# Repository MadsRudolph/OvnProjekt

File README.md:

# 🔥 Ovn-Projekt — Pure Analog & Digital Oven Controller (No MCU)

A fully hardware-based oven control system designed and built with **analog + digital electronics** only — **no microcontroller** or pre-programmed ICs.  
All schematics and PCBs were created in **KiCad**. The final project uses a **hierarchical schematic** so all subsystems connect cleanly in one place.

> This was a tough one: we built the oven before learning every theory detail in class. That made it frustrating at times — and incredibly satisfying when everything finally worked.

---

## 🚀 Quick Start (Open the Project)

1. Open **KiCad 7/8** (tested with 8).
2. Open the **main project**:
   - `./OVN/OVN.kicad_pro`
3. Open the **top schematic**:
   - `./OVN/OVN.kicad_sch`  
   This is the top-level design with a **hierarchical sheet** that pulls in all subsystems (analog control, digital timing/state machine, deviation display, oscillator).
4. Optional: open the **PCB**:
   - `./OVN/OVN.kicad_pcb`

> The subfolders contain **intermediate/local variants** and backups. They’re useful for history, but the **final connected design** lives in `OVN/`.

---

## 🎯 Project Goals

- Automatically cycle between **three set temperatures** (e.g., 50 °C → 110 °C → 80 °C → repeat)
- Hold each temperature for a **fixed duration** (e.g., ~80 s)
- Maintain temperature within **±1 °C** of the target
- Provide **safety shutdown** above a critical threshold (e.g., 130 °C)
- Show **real-time temperature deviation** on an LED bar
- Implement everything with **discrete analog + digital logic** (no MCU/firmware)

---

## 🧩 System Overview

The oven control system is composed of **four main subsystems**:

### 1) Digital Oscillator
Generates clock signals for counters/timers and ADC timing.
- RC network + digital logic
- Adjustable frequency outputs
- Example board size around *35 mm × 47 mm*

### 2) Deviation Display (Afvigelsesdisplay)
Real-time visualization of error between current temperature and setpoint.
- **ADC0804** A/D converter
- **Two 74HC238** decoders → **16 LEDs**
- Center LEDs ≈ in-range (green), outer LEDs ≈ negative/positive deviation

### 3) Analog Control Circuit
Compares measured temperature to selected setpoint and drives the heater.
- Sensor: **LM35**
- **Op-amps** for differential amplification & comparators for thresholds
- **CD4066** analog switch selects between three setpoints
- Provides a scaled signal for the deviation display

### 4) Digital State Machine & Timing
Sequences the temperature program and dwell times.
- **74HC163** counters + combinational logic
- Generates `T1/T2/T3` signals for setpoint selection
- Drives indicators (LEDs / 7-segment) and coordinates timing

---
<h2>🧾 Project Poster</h2>
<p align="center">
  
  <br>
  <em>Click to open the full PDF</em>
</p>
---
## 🛠 Tools & Key Components

- **Design:** KiCad (schematic + PCB)
- **Test Gear:** Multimeter, oscilloscope, logic probes/analyzers
- **Key ICs/Parts:** LM35, ADC0804, 74HC238, 74HC163, CD4066, MCP6002, passives, LEDs

---

## ⚡ Workflow

1. **Subsystem Breadboarding** → validate analog thresholds, timing, and LED decoding  
2. **KiCad Schematic & PCB** → create/clean symbols and **custom footprints** as needed  
3. **Integration** → hierarchical sheet in `OVN` ties everything together  
4. **Debug & Iterate** → scope timing edges, adjust thresholds, verify stability and safety

---

## 🌟 Key Learnings

- Designing robust control with **only analog/digital logic** (no firmware safety net)
- Practical timing, noise, and threshold trade-offs in real hardware
- **KiCad** hierarchical design, footprint creation, and multi-board bring-up
- System-level debugging with mixed-signal interactions

---

## 👥 Team

- **Mads Vølkers Rudolph**  
- **Jonas Beck Jensen**
- **Sigurd Hestbech**
- **Andreas Skaaning**

---

## 🚀 Future Improvements

- MCU-based mode for flexible profiles + logging (keeping the analog chain as backup)
- PID/PI control for even tighter regulation
- Small display (OLED/LCD) with progress and temperature graphs

---

## 🏁 Result

The integrated **OVN** project reflects the **final working oven**:  
- Automatic multi-temperature cycling with dwell times  
- Safety cutoff behavior verified  
- Deviation display and timing logic functioning reliably

**No MCU. Just electrons doing the choreography.**

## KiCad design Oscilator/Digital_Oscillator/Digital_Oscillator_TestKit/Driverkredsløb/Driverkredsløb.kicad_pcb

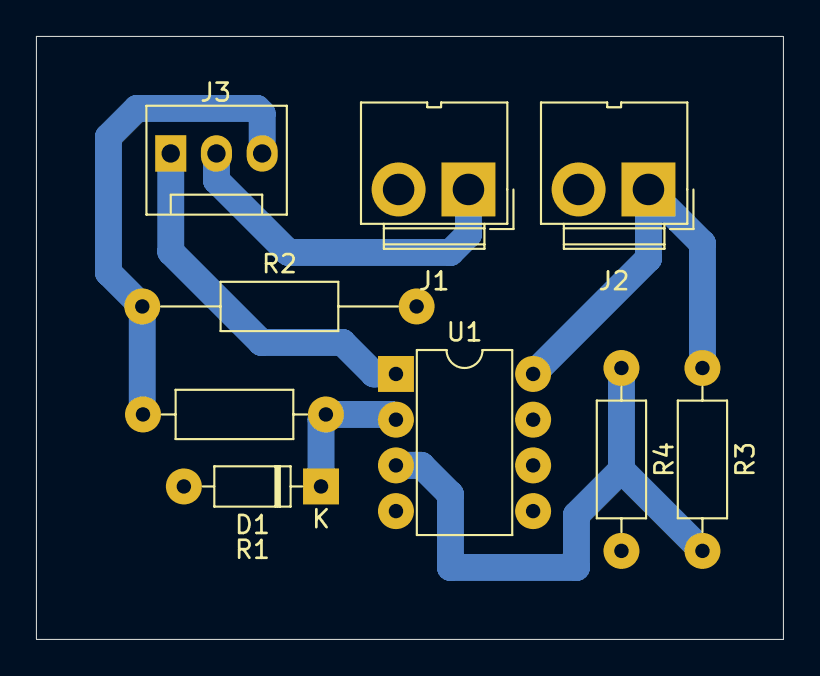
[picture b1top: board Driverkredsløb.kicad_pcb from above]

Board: 2 copper layers, 41.5 x 33.5 mm, 9 parts (0 on the bottom side), 7 nets.

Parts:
D1: 1N4148; D_DO-35_SOD27_P7.62mm_Horizontal
J1, J2: Conn_01x02_Socket; JWT_A3963_1x02_P3.96mm_Vertical
J3: Conn_01x03_Socket; FanPinHeader_1x03_P2.54mm_Vertical
R1: 20k; R_Axial_DIN0207_L6.3mm_D2.5mm_P10.16mm_Horizontal
R2: 0.1; R_Axial_DIN0207_L6.3mm_D2.5mm_P15.24mm_Horizontal
R3: 15k; R_Axial_DIN0207_L6.3mm_D2.5mm_P10.16mm_Horizontal
R4: 300; R_Axial_DIN0207_L6.3mm_D2.5mm_P10.16mm_Horizontal
U1: MCP6002-xMC; DIP-8_W7.62mm

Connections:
GND: J1.2, J2.2, R2.2, R4.2, U1.4 (V-)
unnamed: D1.1 (K), R1.1, U1.2 (-)
unnamed: J1.1, J3.2
unnamed: J2.1, R3.1, U1.8 (V+)
unnamed: J3.1, U1.1
unnamed: J3.3, R1.2, R2.1
unnamed: R3.2, R4.1, U1.3 (+)

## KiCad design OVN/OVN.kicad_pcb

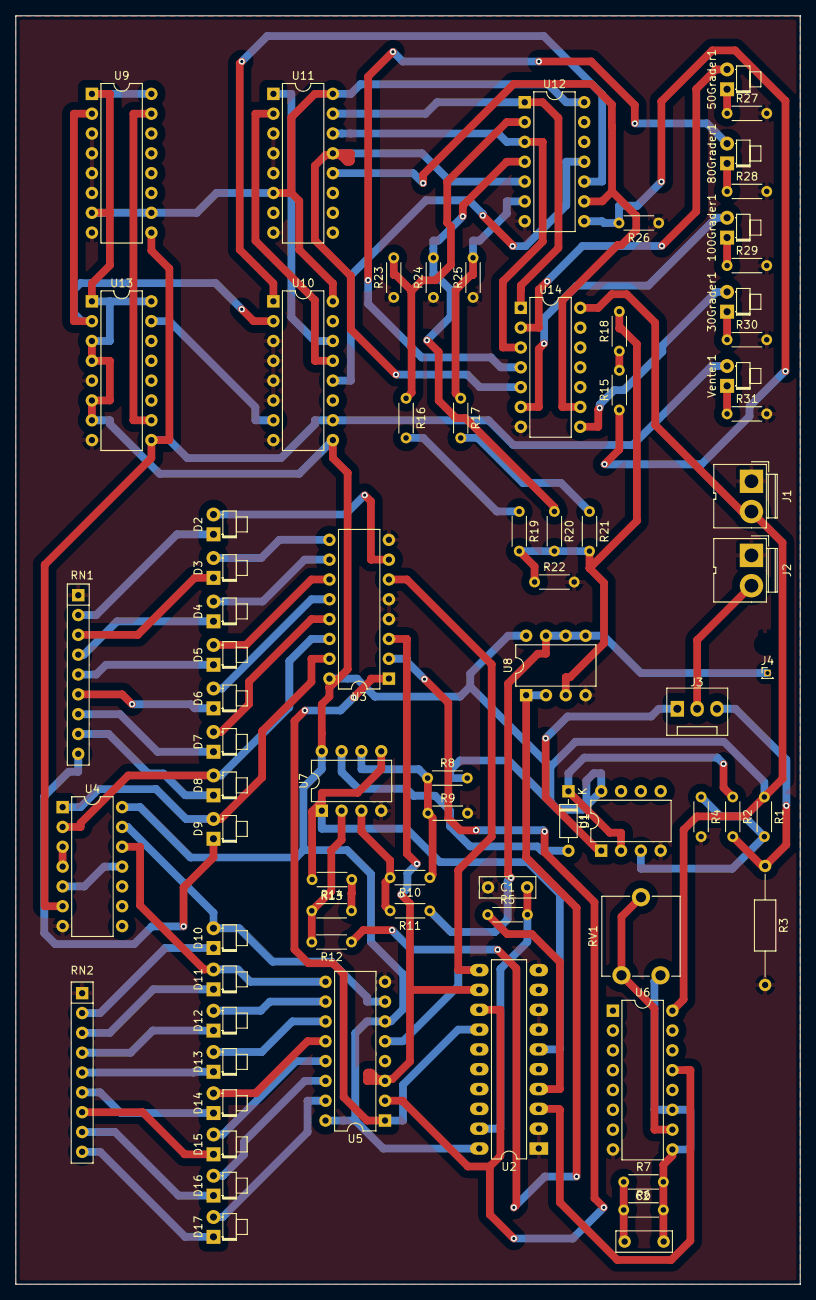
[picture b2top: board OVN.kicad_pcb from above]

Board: 2 copper layers, 100.5 x 162.5 mm, 76 parts (0 on the bottom side), 87 nets.

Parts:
30Grader1, 50Grader1, 80Grader1, 100Grader1: LED; LED_D1.8mm_W1.8mm_H2.4mm_Horizontal_O1.27mm_Z8.2mm
C1: 150nF; C_Disc_D7.0mm_W2.5mm_P5.00mm
C2: 100 nF; C_Disc_D7.0mm_W2.5mm_P5.00mm
D1: 1N4148; D_DO-35_SOD27_P7.62mm_Horizontal
D2, D4, D5, D6, D7, D12, D13, D14, D15, D16, D17: R; LED_D1.8mm_W1.8mm_H2.4mm_Horizontal_O1.27mm_Z8.2mm
D3: LED; LED_D1.8mm_W1.8mm_H2.4mm_Horizontal_O1.27mm_Z8.2mm
D8, D11: GU; LED_D1.8mm_W1.8mm_H2.4mm_Horizontal_O1.27mm_Z8.2mm
D9, D10: GR; LED_D1.8mm_W1.8mm_H2.4mm_Horizontal_O1.27mm_Z8.2mm
J1, J2: Conn_01x02_Pin; JWT_A3963_1x02_P3.96mm_Vertical
J3: Conn_01x03_Socket; FanPinHeader_1x03_P2.54mm_Vertical
J4: LM35; PinHeader_1x01_P1.00mm_Vertical
R1: 15k; R_Axial_DIN0204_L3.6mm_D1.6mm_P5.08mm_Horizontal
R2: 20k; R_Axial_DIN0204_L3.6mm_D1.6mm_P5.08mm_Horizontal
R3: 0.1; R_Axial_DIN0207_L6.3mm_D2.5mm_P15.24mm_Horizontal
R4: 300; R_Axial_DIN0204_L3.6mm_D1.6mm_P5.08mm_Horizontal
R5, R22: 100K; R_Axial_DIN0204_L3.6mm_D1.6mm_P5.08mm_Horizontal
R6: 4.3k; R_Axial_DIN0204_L3.6mm_D1.6mm_P5.08mm_Horizontal
R7: 123K6; R_Axial_DIN0204_L3.6mm_D1.6mm_P5.08mm_Horizontal
R8, R9, R14: 11.5K; R_Axial_DIN0204_L3.6mm_D1.6mm_P5.08mm_Horizontal
R10, R13: 301K; R_Axial_DIN0204_L3.6mm_D1.6mm_P5.08mm_Horizontal
R11, R12: 10K; R_Axial_DIN0204_L3.6mm_D1.6mm_P5.08mm_Horizontal
R15: 787K; R_Axial_DIN0204_L3.6mm_D1.6mm_P5.08mm_Horizontal
R16: 5.6K; R_Axial_DIN0204_L3.6mm_D1.6mm_P5.08mm_Horizontal
R17: 237K; R_Axial_DIN0204_L3.6mm_D1.6mm_P5.08mm_Horizontal
R18: 15K; R_Axial_DIN0204_L3.6mm_D1.6mm_P5.08mm_Horizontal
R19: 475K; R_Axial_DIN0204_L3.6mm_D1.6mm_P5.08mm_Horizontal
R20: 300K; R_Axial_DIN0204_L3.6mm_D1.6mm_P5.08mm_Horizontal
R21: 2.6K; R_Axial_DIN0204_L3.6mm_D1.6mm_P5.08mm_Horizontal
R23, R24, R25, R26, R27, R28, R29, R30, R31: R; R_Axial_DIN0204_L3.6mm_D1.6mm_P5.08mm_Horizontal
RN1, RN2: R_Network08; R_Array_SIP9
RV1: R_Potentiometer_Small; Potentiometer_ACP_CA9-V10_Vertical
U1, U7, U8: MCP6002-xMC; DIP-8_W7.62mm
U2: ADC0804LCN; DIP-20_W7.62mm_LongPads
U3, U5: 74HC238N; DIP-16_W7.62mm
U4: SN74HC86; DIP-14_W7.62mm
U6: 74HC4060; DIP-16_W7.62mm
U9, U10, U13: SN74HC163N; DIP-16_W7.62mm
U11: 74HC138N; DIP-16_W7.62mm
U12, U14: SN74HC04N; DIP-14_W7.62mm
Venter1: LED; LED_D1.8mm_W1.8mm_H2.4mm_Horizontal_O1.27mm_Z8.2mm

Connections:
10V-30V: J2.2, J3.2
+5V: J1.2, R1.1, R8.2, U1.8 (V+), U2.20 (VCC), U3.16 (VCC), U4.14 (VCC), U5.6 (E3), U5.16 (VCC), U6.16 (VDD), U7.8 (V+), U8.8 (V+), U9.1 (~MR), U9.7 (CEP), U9.10 (CET), U9.16 (VCC), U10.9 (~LOAD), U10.16 (VCC), U11.6 (E3), U11.16 (VCC), U12.14 (VCC), U13.1 (~MR), U13.3 (D0), U13.4 (D1), U13.6 (D3), U13.7 (CEP), U13.16 (VCC), U14.14 (VCC)
/ADC Convertor/DB4: U2.14 (DB4), U3.1 (A0), U5.1 (A0)
/ADC Convertor/DB5: U2.13 (DB5), U3.2 (A1), U5.2 (A1)
/ADC Convertor/DB6: U2.12 (DB6), U3.3 (A2), U5.3 (A2)
/ADC Convertor/DB7: U2.11 (DB7), U3.6 (E3), U5.5 (~E2)
/ADC Convertor/WR_in: U2.3 (~WR), U6.13 (Q9), U9.2 (CLK), U10.2 (CLK), U13.2 (CLK)
/Afvigelsesdisplay/Steady state: U4.6 (3Y), U9.9 (~LOAD), U10.10 (CET), U13.9 (~LOAD), Venter1.2 (A)
/Analog styring Differensforstærker/V-Ovn: D1.2 (A), U7.7
/Analog styring spændingsdeler/30°C: R15.1, R26.2, U12.8 (4Y)
/Analog styring spændingsdeler/50°C: R16.1, R23.2, U12.2 (1Y)
/Analog styring spændingsdeler/80°C: R20.1, R24.2, U12.4 (2Y)
/Analog styring spændingsdeler/100°C: R17.1, R25.2, U12.6 (3Y)
Afv_displ_adc: R14.2, U2.6 (VIN(+)), U7.1, U7.5 (+)
GND: C1.1, J1.1, J2.1, R3.2, R4.2, R9.2, R22.2, R23.1, R24.1, R25.1, R26.1, R27.2, R28.2, R29.2, R30.2, R31.2, RN1.1 (common), RN2.1 (common), U1.4 (V-), U2.1 (~CS), U2.2 (~RD), U2.7 (VIN(-)), U2.8 (AGND), U2.10 (DGND), U3.4 (~E1), U3.5 (~E2), U3.8 (GND), U4.7 (GND), U5.4 (~E1), U5.8 (GND), U6.8 (VSS), U6.12 (CLR), U7.4 (V-), U8.4 (V-), U9.3 (D0), U9.4 (D1), U9.5 (D2), U9.6 (D3), U9.8 (GND), U10.3 (D0), U10.4 (D1), U10.5 (D2), U10.6 (D3), U10.8 (GND), U11.3 (A2), U11.4 (~E1), U11.5 (~E2), U11.8 (GND), U12.7 (GND), U13.5 (D2), U13.8 (GND), U14.7 (GND)
LM35_out: J4.1, R11.1, U8.5 (+), U8.6 (-), U8.7
unnamed: 30Grader1.2 (A), U14.8 (4Y)
unnamed: 30Grader1.1 (K), R30.1
unnamed: 50Grader1.2 (A), U14.2 (1Y)
unnamed: 50Grader1.1 (K), R27.1
unnamed: 80Grader1.2 (A), U14.4 (2Y)
unnamed: 80Grader1.1 (K), R28.1
unnamed: 100Grader1.2 (A), U14.6 (3Y)
unnamed: 100Grader1.1 (K), R29.1
unnamed: C2.1, R6.1, R7.1
unnamed: D1.1 (K), R2.1, U1.2 (-)
unnamed: D2.2 (A), U3.7 (Y7)
unnamed: D2.1 (K), RN1.2 (R1)
unnamed: D3.2 (A), U3.9 (Y6)
unnamed: D3.1 (K), RN1.3 (R2)
unnamed: D4.2 (A), U3.10 (Y5)
unnamed: D4.1 (K), RN1.4 (R3)
unnamed: D5.2 (A), U3.11 (Y4)
unnamed: D5.1 (K), RN1.5 (R4)
unnamed: D6.2 (A), U3.12 (Y3)
unnamed: D6.1 (K), RN1.6 (R5)
unnamed: D7.2 (A), U3.13 (Y2)
unnamed: D7.1 (K), RN1.7 (R6)
unnamed: D8.2 (A), U3.14 (Y1), U4.2 (1Y)
unnamed: D8.1 (K), RN1.8 (R7)
unnamed: D9.2 (A), U3.15 (Y0), U4.1 (1A)
unnamed: D9.1 (K), RN1.9 (R8)
unnamed: D10.2 (A), U4.13 (6A), U5.7 (Y7)
unnamed: D10.1 (K), RN2.2 (R1)
unnamed: D11.2 (A), U4.12 (6Y), U5.9 (Y6)
unnamed: D11.1 (K), RN2.3 (R2)
unnamed: D12.2 (A), U5.10 (Y5)
unnamed: D12.1 (K), RN2.4 (R3)
unnamed: D13.2 (A), U5.11 (Y4)
unnamed: D13.1 (K), RN2.5 (R4)
unnamed: D14.2 (A), U5.12 (Y3)
unnamed: D14.1 (K), RN2.6 (R5)
unnamed: D15.2 (A), U5.13 (Y2)
unnamed: D15.1 (K), RN2.7 (R6)
unnamed: D16.2 (A), U5.14 (Y1)
unnamed: D16.1 (K), RN2.8 (R7)
unnamed: D17.2 (A), U5.15 (Y0)
unnamed: D17.1 (K), RN2.9 (R8)
unnamed: J3.1, U1.1
unnamed: J3.3, R2.2, R3.1
unnamed: R13.2, R14.1
unnamed: R15.2, R18.1
unnamed: R16.2, R19.1
unnamed: R17.2, R21.1
unnamed: R1.2, R4.1, U1.3 (+)
unnamed: R5.1, U2.4 (CLK_IN)
unnamed: C1.2, R5.2, U2.19 (CLK_R)
unnamed: U4.3 (2A), U4.4 (2Y)
unnamed: U4.5 (3A), U4.11 (5A)
unnamed: C2.2, R6.2, R7.2, RV1.1, U6.9 (~Φ0), U6.11 (~Φ1)
unnamed: RV1.2, RV1.3, U6.10 (Φ0)
unnamed: R10.2, R11.2, U7.3 (+)
unnamed: R12.2, R13.1, U7.2 (-)
unnamed: R8.1, R9.1, R10.1, U7.6 (-)
unnamed: R18.2, R19.2, R20.2, R21.2, R22.1, U8.3 (+)
unnamed: U10.7 (CEP), U13.15 (TC)
unnamed: U10.14 (Q0), U11.1 (A0)
unnamed: U10.13 (Q1), U11.2 (A1)
unnamed: U10.12 (Q2), U12.11 (5A)
unnamed: U10.1 (~MR), U12.10 (5Y)
unnamed: U11.15 (Y0), U12.1 (1A), U14.1 (1A)
unnamed: U11.14 (Y1), U12.3 (2A), U14.3 (2A)
unnamed: U11.13 (Y2), U12.5 (3A), U14.5 (3A)
unnamed: U11.12 (Y3), U12.9 (4A), U14.9 (4A)
unnamed: U9.15 (TC), U13.10 (CET)
unnamed: R31.1, Venter1.1 (K)
Sp_v: R12.1, U8.1, U8.2 (-)

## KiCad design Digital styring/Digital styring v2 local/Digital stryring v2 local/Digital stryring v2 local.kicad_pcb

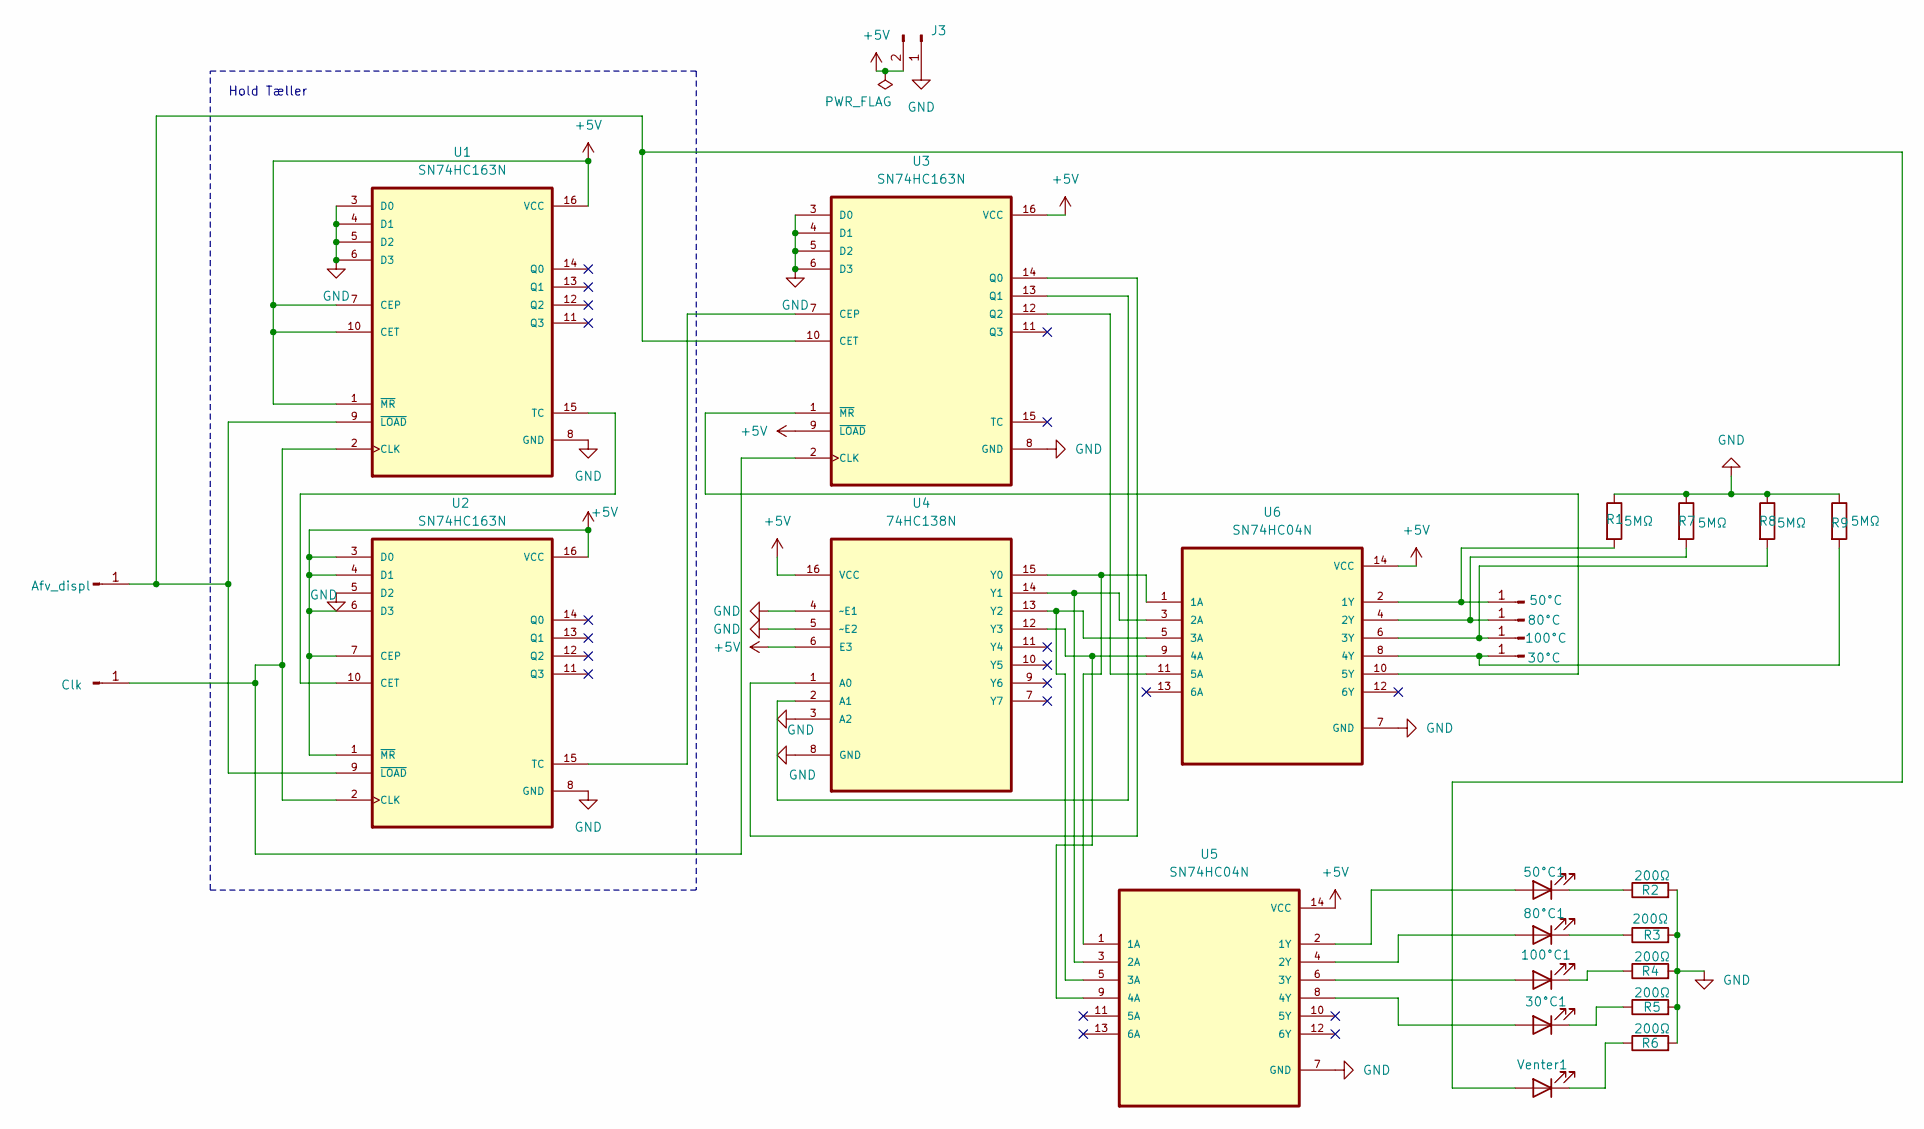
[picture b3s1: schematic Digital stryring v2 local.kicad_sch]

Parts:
30°C1, 50°C1, 80°C1, 100°C1: LED; LED_D1.8mm_W1.8mm_H2.4mm_Horizontal_O1.27mm_Z8.2mm
J1: Afv_displ; PinHeader_1x01_P1.00mm_Vertical
J2: Clk; PinHeader_1x01_P1.00mm_Vertical
J3: Conn_01x02_Pin; JWT_A3963_1x02_P3.96mm_Vertical
J4: 50°C; PinHeader_1x01_P1.00mm_Vertical
J5: 80°C; PinHeader_1x01_P1.00mm_Vertical
J6: 100°C; PinHeader_1x01_P1.00mm_Vertical
J7: 30°C; PinHeader_1x01_P1.00mm_Vertical
R1, R7, R8, R9: 5MΩ; R_Axial_DIN0204_L3.6mm_D1.6mm_P7.62mm_Horizontal
R2, R3, R4, R5, R6: 200Ω; R_Axial_DIN0204_L3.6mm_D1.6mm_P5.08mm_Horizontal
U1, U2, U3: SN74HC163N; DIP-16_W7.62mm
U4: 74HC138N; DIP-16_W7.62mm; MPN 74HC238N
U5, U6: SN74HC04N; DIP-14_W7.62mm
Venter1: LED; LED_D1.8mm_W1.8mm_H2.4mm_Horizontal_O1.27mm_Z8.2mm

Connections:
+5V: J3.2, U1.1 (~MR), U1.7 (CEP), U1.10 (CET), U1.16 (VCC), U2.1 (~MR), U2.3 (D0), U2.4 (D1), U2.6 (D3), U2.7 (CEP), U2.16 (VCC), U3.9 (~LOAD), U3.16 (VCC), U4.6 (E3), U4.16 (VCC), U5.14 (VCC), U6.14 (VCC)
GND: J3.1, R1.1, R2.2, R3.2, R4.2, R5.2, R6.2, R7.1, R8.1, R9.1, U1.3 (D0), U1.4 (D1), U1.5 (D2), U1.6 (D3), U1.8 (GND), U2.5 (D2), U2.8 (GND), U3.3 (D0), U3.4 (D1), U3.5 (D2), U3.6 (D3), U3.8 (GND), U4.3 (A2), U4.4 (~E1), U4.5 (~E2), U4.8 (GND), U5.7 (GND), U6.7 (GND)
unnamed: 30°C1.2 (A), U5.8 (4Y)
unnamed: 30°C1.1 (K), R5.1
unnamed: 50°C1.2 (A), U5.2 (1Y)
unnamed: 50°C1.1 (K), R2.1
unnamed: 80°C1.2 (A), U5.4 (2Y)
unnamed: 80°C1.1 (K), R3.1
unnamed: 100°C1.2 (A), U5.6 (3Y)
unnamed: 100°C1.1 (K), R4.1
unnamed: J1.1, U1.9 (~LOAD), U2.9 (~LOAD), U3.10 (CET), Venter1.2 (A)
unnamed: J2.1, U1.2 (CLK), U2.2 (CLK), U3.2 (CLK)
unnamed: J4.1, R1.2, U6.2 (1Y)
unnamed: J5.1, R7.2, U6.4 (2Y)
unnamed: J6.1, R8.2, U6.6 (3Y)
unnamed: J7.1, R9.2, U6.8 (4Y)
unnamed: U1.15 (TC), U2.10 (CET)
unnamed: U2.15 (TC), U3.7 (CEP)
unnamed: U3.14 (Q0), U4.1 (A0)
unnamed: U3.13 (Q1), U4.2 (A1)
unnamed: U3.12 (Q2), U6.11 (5A)
unnamed: U3.1 (~MR), U6.10 (5Y)
unnamed: U4.15 (Y0), U5.1 (1A), U6.1 (1A)
unnamed: U4.14 (Y1), U5.3 (2A), U6.3 (2A)
unnamed: U4.13 (Y2), U5.5 (3A), U6.5 (3A)
unnamed: U4.12 (Y3), U5.9 (4A), U6.9 (4A)
unnamed: R6.1, Venter1.1 (K)

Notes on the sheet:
Hold Tæller

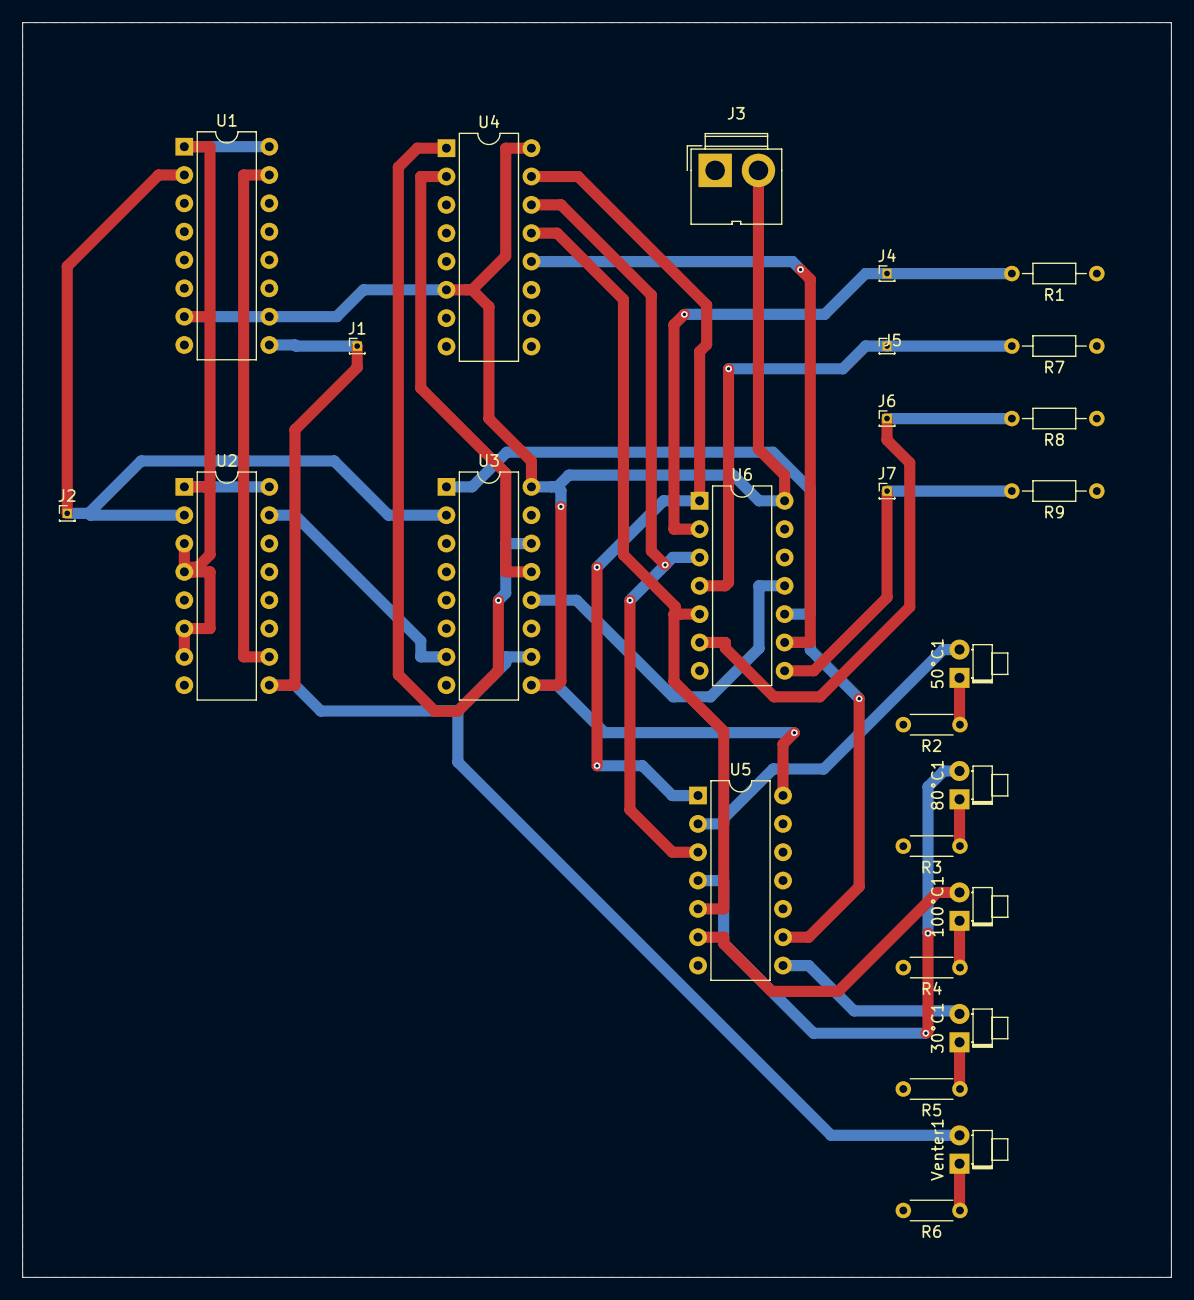
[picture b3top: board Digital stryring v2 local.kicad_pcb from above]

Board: 2 copper layers, 103.0 x 112.5 mm, 27 parts (0 on the bottom side), 27 nets.

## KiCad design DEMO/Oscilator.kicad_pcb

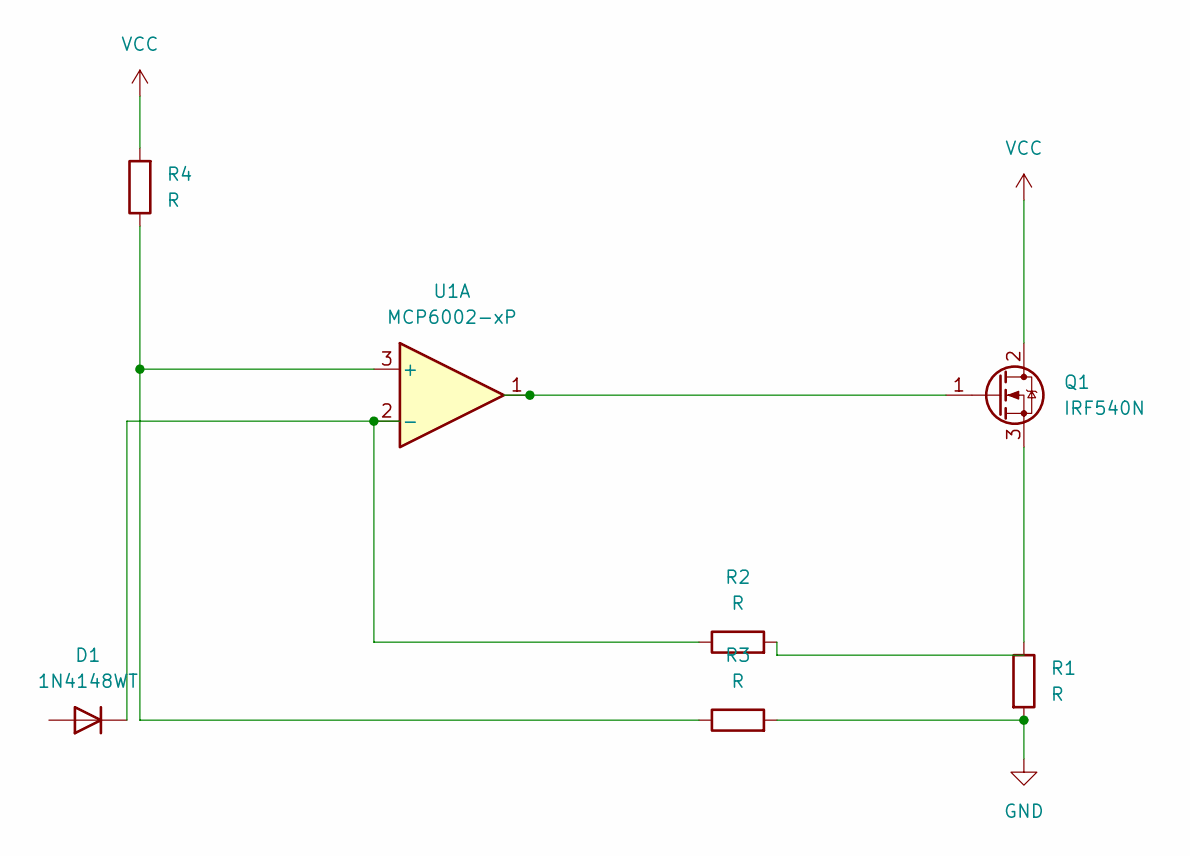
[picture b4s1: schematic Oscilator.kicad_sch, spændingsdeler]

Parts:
D1: 1N4148WT; D_SOD-523
Q1: IRF540N; TO-220-3_Vertical
R1, R2, R3, R4: R; R_Axial_DIN0207_L6.3mm_D2.5mm_P7.62mm_Horizontal
U1: MCP6002-xP; CERDIP-8_W7.62mm_SideBrazed_Socket

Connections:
GND: R1.2, R3.2
unnamed: D1.1 (K), R2.1, U1.2 (-)
unnamed: Q1.1 (G), U1.1
unnamed: Q1.3 (S), R1.1
unnamed: R3.1, R4.1, U1.3 (+)
VCC: Q1.2 (D), R4.2

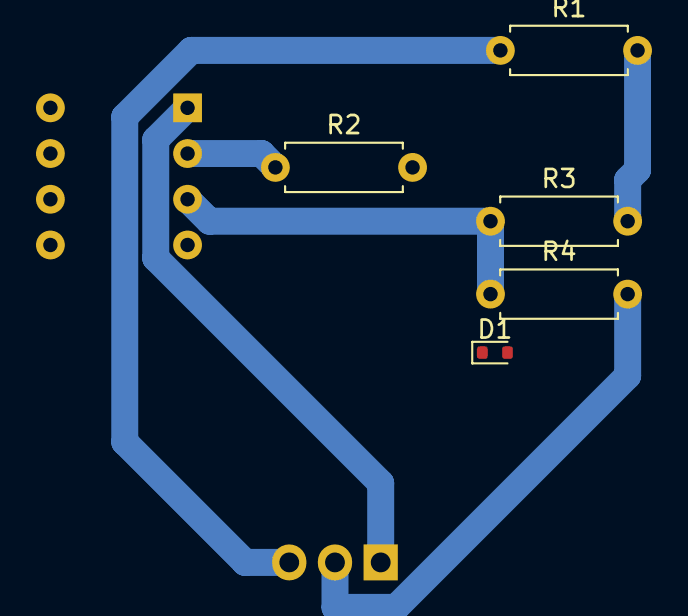
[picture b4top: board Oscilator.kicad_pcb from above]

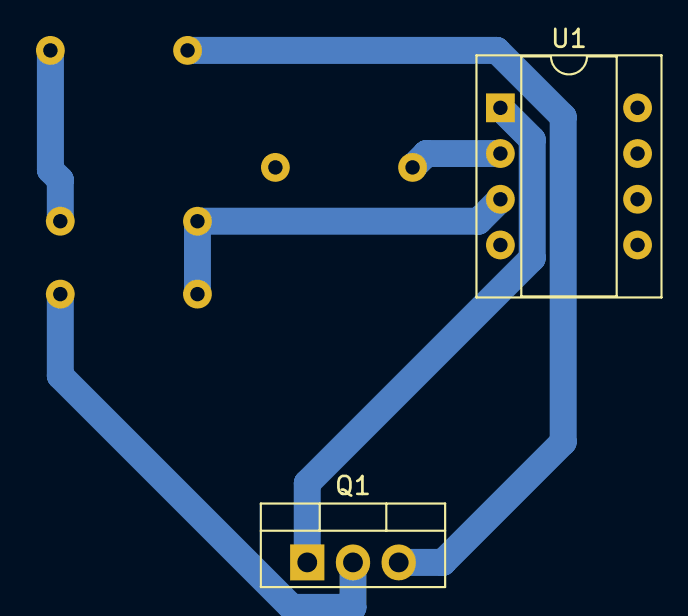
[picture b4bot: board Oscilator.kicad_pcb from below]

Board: 2 copper layers, 7 parts (2 on the bottom side), 6 nets.

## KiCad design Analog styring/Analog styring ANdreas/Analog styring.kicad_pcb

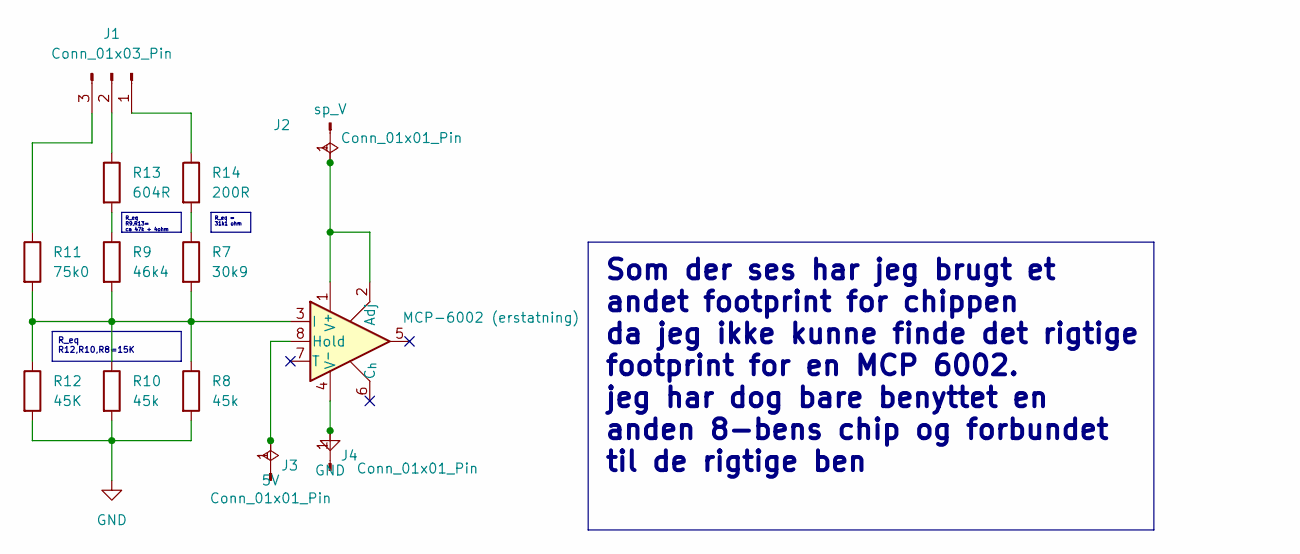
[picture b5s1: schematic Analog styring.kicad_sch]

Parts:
J1: Conn_01x03_Pin; FanPinHeader_1x03_P2.54mm_Vertical
J2, J3, J4: Conn_01x01_Pin; PinHeader_1x01_P1.00mm_Vertical
R7: 30k9; R_Axial_DIN0204_L3.6mm_D1.6mm_P2.54mm_Vertical
R8, R10: 45k; R_Axial_DIN0204_L3.6mm_D1.6mm_P2.54mm_Vertical
R9: 46k4; R_Axial_DIN0204_L3.6mm_D1.6mm_P2.54mm_Vertical
R11: 75k0; R_Axial_DIN0204_L3.6mm_D1.6mm_P2.54mm_Vertical
R12: 45K; R_Axial_DIN0204_L3.6mm_D1.6mm_P2.54mm_Vertical
R13: 604R; R_Axial_DIN0204_L3.6mm_D1.6mm_P2.54mm_Vertical
R14: 200R; R_Axial_DIN0204_L3.6mm_D1.6mm_P2.54mm_Vertical
U1: MCP-6002 (erstatning); DIP-8_W7.62mm

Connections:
GND: J4.1, R8.2, R10.2, R12.2, U1.4 (V^{-})
unnamed: J1.1, R14.1
unnamed: J1.2, R13.1
unnamed: J1.3, R11.1
unnamed: J2.1, U1.1 (V^{+}), U1.2 (Adj)
unnamed: J3.1, U1.8 (Hold)
unnamed: R9.1, R13.2
unnamed: R7.1, R14.2
unnamed: R7.2, R8.1, R9.2, R10.1, R11.2, R12.1, U1.3 (I)

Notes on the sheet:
Som der ses har jeg brugt et andet footprint for chippen da jeg ikke kunne finde det rigtige footprint for en MCP 6002. jeg har dog bare benyttet en anden 8-bens chip og forbundet til de rigtige ben
R_eq R9,R13= ca 47k + 4ohm
R_eq R12,R10,R8=15K
R_eq = 31k1 ohm

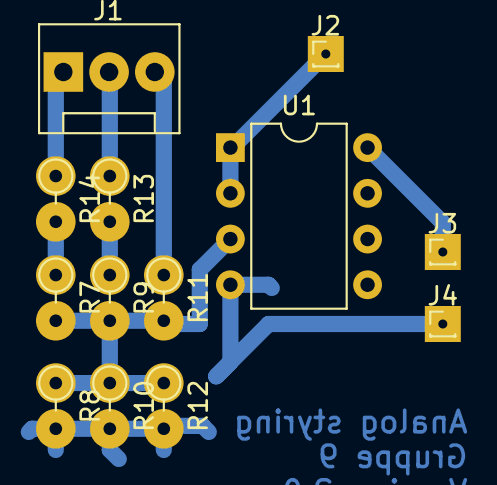
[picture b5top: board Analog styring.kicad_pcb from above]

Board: 2 copper layers, 13 parts (0 on the bottom side), 9 nets.

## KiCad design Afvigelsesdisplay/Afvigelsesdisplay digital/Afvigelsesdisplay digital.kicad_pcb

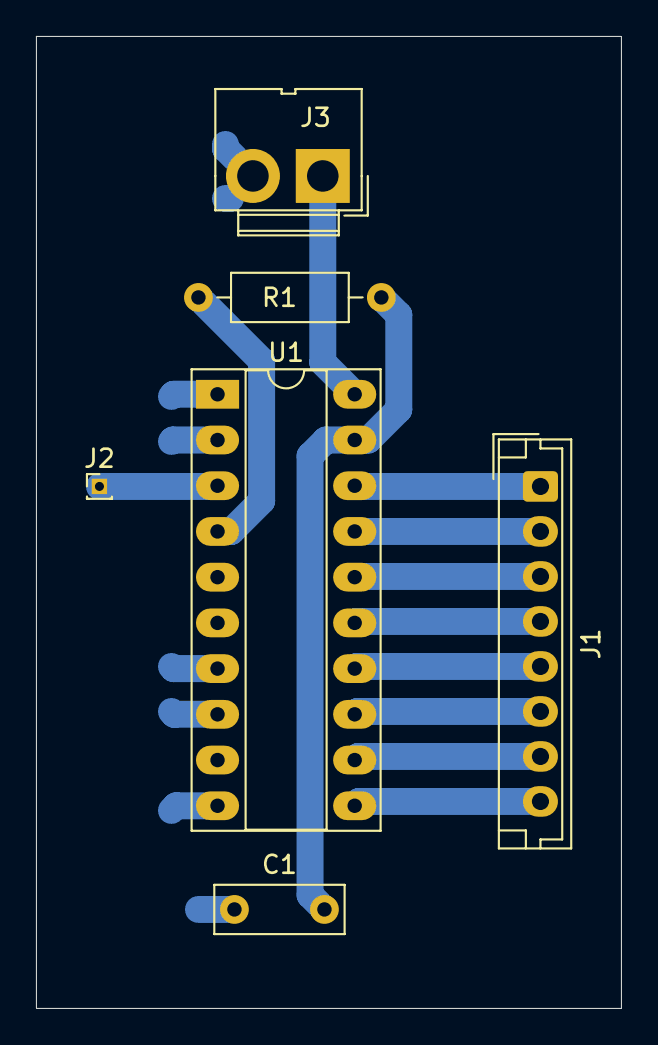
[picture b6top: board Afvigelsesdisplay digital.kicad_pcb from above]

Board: 2 copper layers, 32.5 x 54.0 mm, 6 parts (0 on the bottom side), 13 nets.

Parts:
C1: 150nF; C_Disc_D7.0mm_W2.5mm_P5.00mm
J1: Conn_01x08_Socket; JST_EH_B8B-EH-A_1x08_P2.50mm_Vertical
J2: Conn_01x01_Pin; PinHeader_1x01_P1.00mm_Vertical
J3: Conn_01x02_Pin; JWT_A3963_1x02_P3.96mm_Vertical
R1: 100K; R_Axial_DIN0207_L6.3mm_D2.5mm_P10.16mm_Horizontal
U1: ADC0804LCN; CERDIP-20_W7.62mm_SideBrazed_LongPads_Socket

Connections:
GND: C1.1, J3.2, U1.1 (~CS), U1.2 (~RD), U1.7 (VIN(-)), U1.8 (AGND), U1.10 (DGND)
unnamed: J1.1, U1.18 (DB0)
unnamed: J1.2, U1.17 (DB1)
unnamed: J1.3, U1.16 (DB2)
unnamed: J1.4, U1.15 (DB3)
unnamed: J1.5, U1.14 (DB4)
unnamed: J1.6, U1.13 (DB5)
unnamed: J1.7, U1.12 (DB6)
unnamed: J1.8, U1.11 (DB7)
unnamed: J2.1, U1.3 (~WR)
unnamed: R1.1, U1.4 (CLK_IN)
unnamed: C1.2, R1.2, U1.19 (CLK_R)
VCC: J3.1, U1.20 (VCC)

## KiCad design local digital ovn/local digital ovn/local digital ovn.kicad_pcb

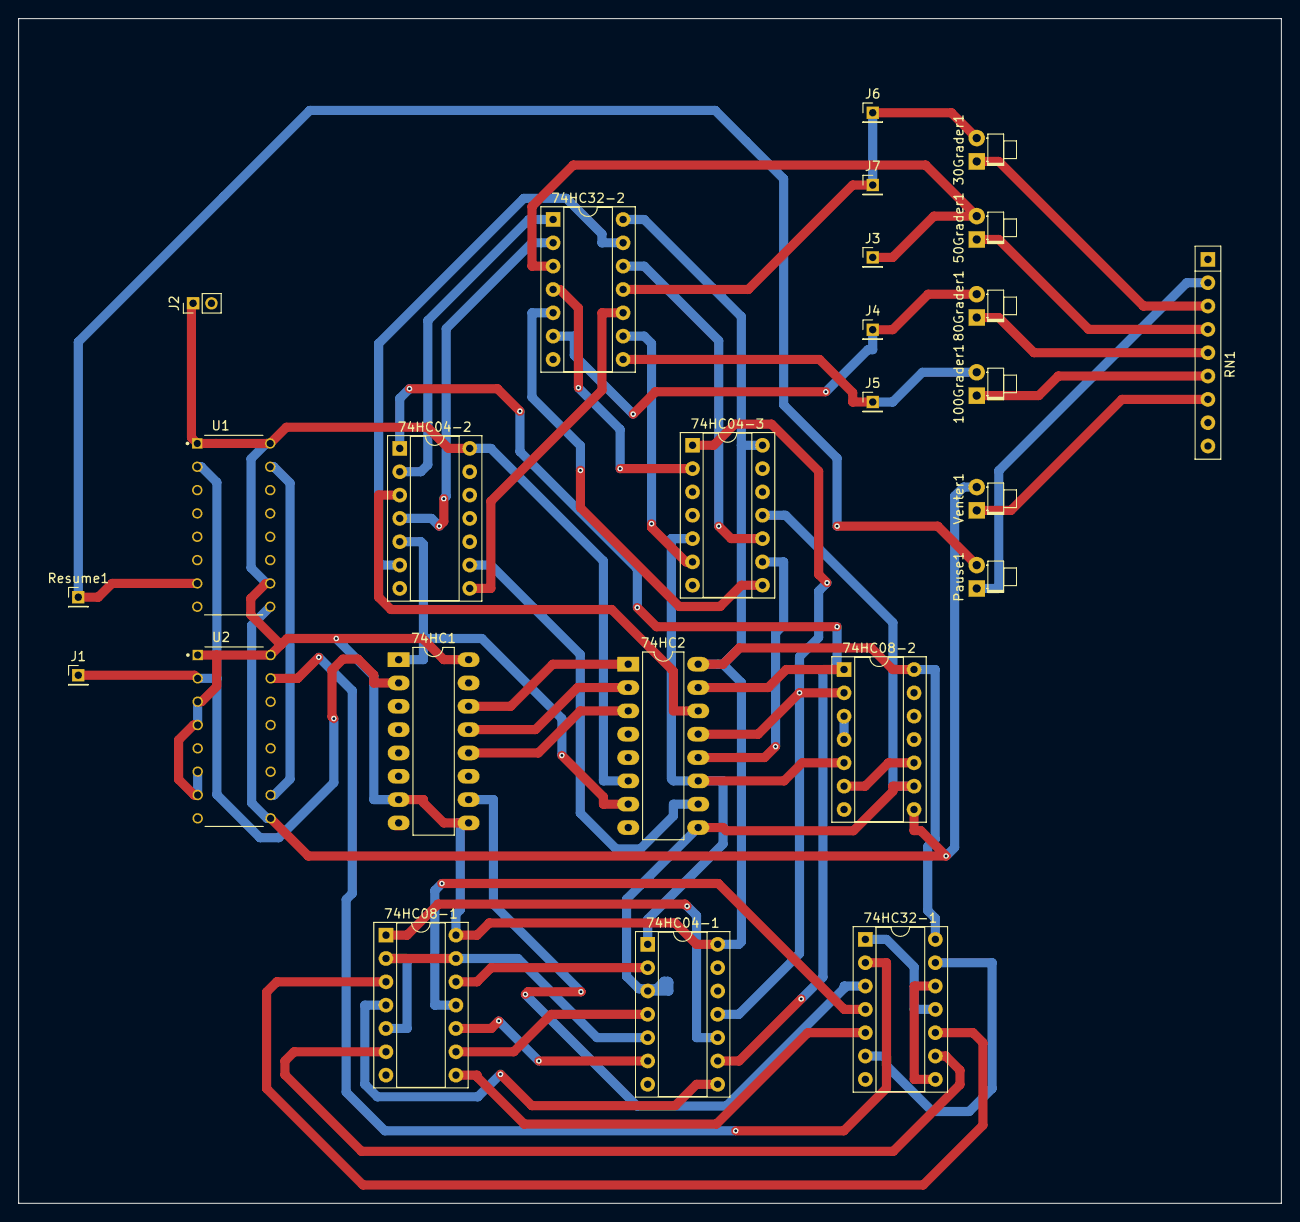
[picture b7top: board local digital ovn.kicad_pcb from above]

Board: 2 copper layers, 137.5 x 129.0 mm, 26 parts (0 on the bottom side), 52 nets.

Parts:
30Grader1, 50Grader1, 80Grader1, 100Grader1: LED; LED_D1.8mm_W1.8mm_H2.4mm_Horizontal_O1.27mm_Z8.2mm
74HC1, 74HC2: DIP-16_W7.62mm_LongPads
74HC04-1, 74HC04-2, 74HC04-3, 74HC08-1, 74HC08-2, 74HC32-1, 74HC32-2: DIP-14_W7.62mm_Socket
J1: 1Hz; PinHeader_1x01_P2.00mm_Vertical
J2: Conn_01x02_Pin; PinHeader_1x02_P2.00mm_Vertical
J3: 50 Grader; PinHeader_1x01_P2.00mm_Vertical
J4: 80 Grader; PinHeader_1x01_P2.00mm_Vertical
J5: 100 grader; PinHeader_1x01_P2.00mm_Vertical
J6: Blæser; PinHeader_1x01_P2.00mm_Vertical
J7: 30 Grader; PinHeader_1x01_P2.00mm_Vertical
Pause1: LED; LED_D1.8mm_W1.8mm_H2.4mm_Horizontal_O1.27mm_Z8.2mm
RN1: R_Network08; R_Array_SIP9
Resume1: PinHeader_1x01_P2.00mm_Vertical
U1, U2: SN74HC163N; DIP794W45P254L1969H508Q16
Venter1: LED; LED_D1.8mm_W1.8mm_H2.4mm_Horizontal_O1.27mm_Z8.2mm

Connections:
+5V: 74HC1.7 (CEP), 74HC1.9 (Load), 74HC1.16 (Vcc), 74HC2.6 (E3), 74HC2.16 (Vcc), 74HC04-1.14 (Vcc), 74HC04-2.14 (Vcc), 74HC04-3.14 (Vcc), 74HC08-1.14 (Vcc), 74HC08-2.14 (Vcc), 74HC32-1.14 (Vcc), 74HC32-2.14 (Vcc), J2.1, U1.1 (~MR), U1.10 (CET), U1.16 (VCC), U2.1 (~MR), U2.3 (D0), U2.4 (D1), U2.6 (D3), U2.7 (CEP), U2.16 (VCC)
/30 C: 30Grader1.2 (A), 74HC32-2.11 (4Y), J6.1, J7.1
/50 C: 50Grader1.2 (A), 74HC32-2.3 (1Y), J3.1
/80 C: 74HC32-2.6 (2Y), 80Grader1.2 (A), J4.1
/100 C: 74HC32-2.8 (3Y), 100Grader1.2 (A), J5.1
/Clk 1Hz: 74HC1.2 (CP), J1.1, U1.2 (CLK), U2.2 (CLK)
/Resume: Pause1.2 (A), Resume1.1, U1.7 (CEP)
/komparator input: 74HC04-1.5 (3A), 74HC08-1.2 (1B), 74HC08-1.5 (2B), 74HC08-1.13 (4B)
GND: 74HC1.3 (D0), 74HC1.4 (D1), 74HC1.5 (D2), 74HC1.6 (D3), 74HC1.8 (GND), 74HC2.4 (E1), 74HC2.5 (E2), 74HC2.8 (GND), 74HC04-1.7 (GND), 74HC04-2.7 (GND), 74HC04-3.7 (GND), 74HC08-1.7 (GND), 74HC08-2.7 (GND), 74HC32-1.7 (GND), 74HC32-2.7 (GND), J2.2, RN1.1 (common), U1.3 (D0), U1.4 (D1), U1.5 (D2), U1.6 (D3), U1.8 (GND), U2.5 (D2), U2.8 (GND)
unnamed: 30Grader1.1 (K), RN1.3 (R2)
unnamed: 50Grader1.1 (K), RN1.4 (R3)
unnamed: 74HC1.10 (CET), 74HC32-1.3 (1Y)
unnamed: 74HC1.14 (Q0), 74HC2.1 (A0)
unnamed: 74HC1.13 (Q1), 74HC2.2 (A1)
unnamed: 74HC1.12 (Q2), 74HC2.3 (A3)
unnamed: 74HC2.11 (Y4), 74HC04-1.1 (1A), 74HC04-3.5 (3A), 74HC08-2.5 (2B)
unnamed: 74HC04-1.2 (1Y), 74HC08-1.12 (4A)
unnamed: 74HC2.9 (Y6), 74HC04-1.3 (2A), 74HC04-3.11 (5A), 74HC08-2.9 (3A)
unnamed: 74HC04-1.4 (2Y), 74HC08-1.9 (3A)
unnamed: 74HC04-1.6 (3Y), 74HC08-1.10 (3B)
unnamed: 74HC2.15 (Y0), 74HC04-1.9 (4A), 74HC04-2.1 (1A), 74HC08-2.1 (1A)
unnamed: 74HC04-1.8 (4Y), 74HC08-1.4 (2A)
unnamed: 74HC2.13 (Y2), 74HC04-1.11 (5A), 74HC04-3.1 (1A), 74HC08-2.2 (1B)
unnamed: 74HC04-1.10 (5Y), 74HC08-1.1 (1A)
unnamed: 74HC04-2.2 (1Y), 74HC32-2.1 (1A)
unnamed: 74HC2.14 (Y1), 74HC04-2.3 (2A)
unnamed: 74HC04-2.4 (2Y), 74HC32-2.2 (1B)
unnamed: 74HC1.1 (MR), 74HC2.7 (Y7), 74HC04-2.5 (3A)
unnamed: 74HC04-2.6 (3Y), 74HC32-2.13 (4B)
unnamed: 74HC2.10 (Y5), 74HC04-2.9 (4A)
unnamed: 74HC04-2.8 (4Y), 74HC32-2.10 (3B)
unnamed: 74HC04-3.2 (1Y), 74HC32-2.4 (2A)
unnamed: 74HC04-3.6 (3Y), 74HC32-2.9 (3A)
unnamed: 74HC2.12 (Y3), 74HC04-3.9 (4A)
unnamed: 74HC04-3.8 (4Y), 74HC32-2.5 (2B)
unnamed: 74HC04-3.10 (5Y), 74HC32-2.12 (4A)
unnamed: 74HC08-1.3 (1Y), 74HC32-1.10 (3B)
unnamed: 74HC08-1.6 (2Y), 74HC32-1.9 (3A)
unnamed: 74HC08-1.8 (3Y), 74HC32-1.5 (2B)
unnamed: 74HC08-1.11 (4Y), 74HC32-1.4 (2A)
unnamed: 74HC08-2.3 (1Y), 74HC08-2.4 (2A)
unnamed: 74HC08-2.6 (2Y), 74HC08-2.10 (3B)
unnamed: 74HC08-2.8 (3Y), U1.9 (~LOAD), U2.9 (~LOAD), Venter1.2 (A)
unnamed: 74HC32-1.1 (1A), 74HC32-1.11 (4Y)
unnamed: 74HC32-1.2 (1B), U2.15 (TC)
unnamed: 74HC32-1.6 (2Y), 74HC32-1.13 (4B)
unnamed: 74HC32-1.8 (3Y), 74HC32-1.12 (4A)
unnamed: 80Grader1.1 (K), RN1.5 (R4)
unnamed: 100Grader1.1 (K), RN1.6 (R5)
unnamed: Pause1.1 (K), RN1.2 (R1)
unnamed: RN1.7 (R6), Venter1.1 (K)
unnamed: U1.15 (TC), U2.10 (CET)

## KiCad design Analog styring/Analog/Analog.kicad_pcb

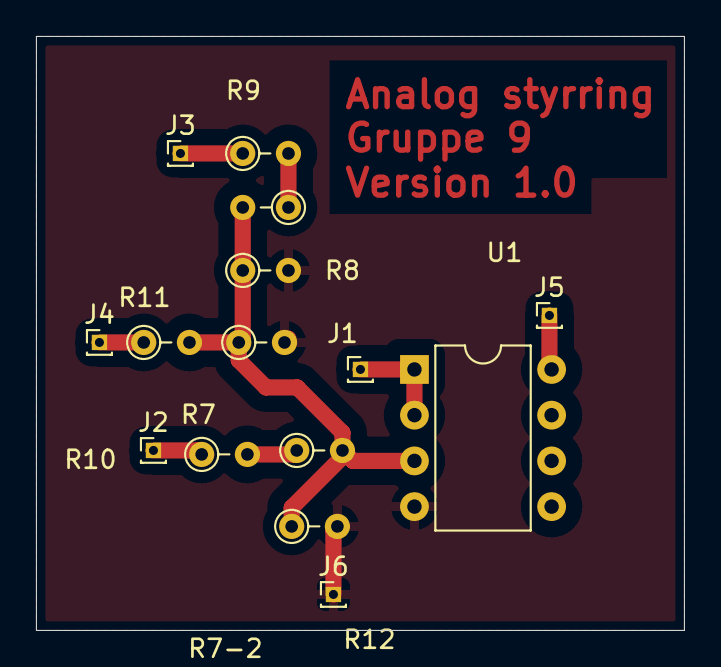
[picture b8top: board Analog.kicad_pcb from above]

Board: 2 copper layers, 36.0 x 33.0 mm, 15 parts (0 on the bottom side), 9 nets.

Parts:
J1, J2, J3, J4, J5, J6: Conn_01x01_Pin; PinHeader_1x01_P1.00mm_Vertical
R7: 200R; R_Axial_DIN0204_L3.6mm_D1.6mm_P2.54mm_Vertical
R7-2: 30K9; R_Axial_DIN0204_L3.6mm_D1.6mm_P2.54mm_Vertical
R8, R10, R12: 45K; R_Axial_DIN0204_L3.6mm_D1.6mm_P2.54mm_Vertical
R9: 604R; R_Axial_DIN0204_L3.6mm_D1.6mm_P2.54mm_Vertical
R9-2: 46K4; R_Axial_DIN0204_L3.6mm_D1.6mm_P2.54mm_Vertical
R11: 75K; R_Axial_DIN0204_L3.6mm_D1.6mm_P2.54mm_Vertical
U1: LF398_DIP8; DIP-8_W7.62mm

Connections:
Earth: J6.1, R8.2, R10.2, R12.2, U1.4 (V^{-})
unnamed: J1.1, U1.1 (V^{+}), U1.2 (Adj)
unnamed: J2.1, R7.1
unnamed: J3.1, R9.1
unnamed: J4.1, R11.1
unnamed: J5.1, U1.8 (Hold)
unnamed: R7.2, R7-2.1
unnamed: R9.2, R9-2.1
unnamed: R7-2.2, R8.1, R9-2.2, R10.1, R11.2, R12.1, U1.3 (I)

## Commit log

2025-09-05 Initial commit of Ovn Project
2025-09-22 Added poster
